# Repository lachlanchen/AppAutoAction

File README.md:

[English](README.md) · [العربية](i18n/README.ar.md) · [Español](i18n/README.es.md) · [Français](i18n/README.fr.md) · [日本語](i18n/README.ja.md) · [한국어](i18n/README.ko.md) · [Tiếng Việt](i18n/README.vi.md) · [中文 (简体)](i18n/README.zh-Hans.md) · [中文（繁體）](i18n/README.zh-Hant.md) · [Deutsch](i18n/README.de.md) · [Русский](i18n/README.ru.md)

<p align="center">

</p>

<h1 align="center">AgInTi LabCanvas</h1>

<p align="center">
  Agent routing for Blender, BioRender, Unity, Unreal, and future creative tools.
  AgInTi LabCanvas gives Codex, AgInTiFlow, Claude, local LLMs, and other MCP-aware agents one practical control plane for app automation.
</p>

<p align="center">
  <a href="#quick-start">Quick Start</a> ·
  <a href="#paper-figure-studio">Paper Figures</a> ·
  <a href="#3d-experiment-design">3D Design</a> ·
  <a href="#targets">Targets</a> ·
  <a href="#research-backed-design">Research</a> ·
  <a href="#languages">Languages</a>
</p>

<p align="center">
  Live studio demo: chat asks for a V-SPICE experiment setup, OpenSCAD exports the CAD proxy, and Blender renders the selected right-side canvas artifact.
</p>

## Why This Exists

Creative tools are gaining agent bridges, but each bridge has a different install path, port, protocol, and safety model. AgInTi LabCanvas keeps those targets in one registry, validates them, emits MCP client config, and dispatches dry-run or live JSON envelopes to the right adapter.

It is intentionally small: Python standard library, explicit config, no hidden editor automation.

## Quick Start

Install from npm:

```bash
npm install -g @lazyingart/labcanvas
labcanvas --version
labcanvas webapp start --port 19473
```

Or run from a source checkout:

```bash
PYTHONPATH=src python -m agenticapp list
PYTHONPATH=src python -m agenticapp doctor
PYTHONPATH=src python -m agenticapp dispatch blender "Create a red cube at the origin" --dry-run
PYTHONPATH=src python -m agenticapp mcp-config
PYTHONPATH=src python -m agenticapp studio status
PYTHONPATH=src python -m unittest discover -s tests
```

After installation, the console command is also available as:

```bash
labcanvas list
labcanvas dispatch unity "Create a test scene with three labeled cubes" --dry-run
labcanvas studio figure-grid "optical device icons 2x3" --rows 2 --cols 3
labcanvas webapp start --port 19473
```

## Paper Figure Studio

```bash
labcanvas web --port 8787 --open
```

The web app now has a bright-by-default theme, chat panel, artifact canvas, scene editor, and backend settings. It can:

- Switch the visible studio UI across the same 11 languages as the localized READMEs.
- Treat generated overview images as concepts, then decompose them into editable atomic parts.
- Generate exact `NxM` SVG paper-figure grids with black panel boundaries.
- Prepare AgInTi image-generation dry-run payloads for scientific icon concepts.
- Store BioRender MCP settings without storing secrets.
- Export the current scene to OpenSCAD for mechanical layout planning.
- Render the scene through Blender and preview PNG, `.blend`, `.scad`, JSON, and text artifacts.
- Toggle Blender, OpenSCAD, AgInTi image generation, BioRender MCP, and target-registry routing settings.
- Dry-run any configured target from the studio and save the dispatch envelope as a canvas artifact.

Artifacts are tracked under `output/webapp/artifacts.json` and served in the canvas rail. The intended figure architecture is documented in [docs/EDITABLE_FIGURE_PIPELINE.md](docs/EDITABLE_FIGURE_PIPELINE.md). See also [docs/PAPER_FIGURE_STUDIO.md](docs/PAPER_FIGURE_STUDIO.md), [docs/STUDIO_CLI.md](docs/STUDIO_CLI.md), [docs/WEBAPP.md](docs/WEBAPP.md), and [docs/NPM.md](docs/NPM.md).

## 3D Experiment Design

AgInTi LabCanvas now includes a systematic Blender workflow for paper setup figures, optical benches, device concepts, and experiment design:

```bash
labcanvas web --port 8787 --open
labcanvas scene-template experiment-setup --output my-setup.scene.json
labcanvas render-scene my-setup.scene.json --dry-run
labcanvas render-scene my-setup.scene.json --output-dir output/scenes
```

The web app provides chat, JSON scene editing, dry-run planning, and render preview. The source of truth is a JSON scene spec. Blender runs headless and produces a `.png` preview plus a `.blend` scene. Start from [examples/paper-optics-setup.scene.json](examples/paper-optics-setup.scene.json), inspect the generated [example render](examples/renders/paper-optics-setup.png), or read [docs/WEBAPP.md](docs/WEBAPP.md) and [docs/SCENE_SPEC.md](docs/SCENE_SPEC.md).

CAD hardware notes now live in [cad/README.md](cad/README.md), including the OpenHI/Nature STEP import notes and a parametric [C-mount reflector adapter](cad/designs/cmount_reflector_adapter/README.md). JLCPCB/Jialichuang automation research is documented in [pcb/jlcpcb-jialichuang-automation.md](pcb/jlcpcb-jialichuang-automation.md).

## Local Blender Test

For a no-sudo local Blender install and a real headless scene generation test:

```bash
scripts/install_blender_portable.sh
labcanvas --config configs/blender-local-command.example.json doctor
labcanvas --config configs/blender-local-command.example.json dispatch blender "Draw a welcoming modern building with a tower"
```

The command bridge is [bridges/codex_exec_blender.sh](bridges/codex_exec_blender.sh). It reads the AgInTi LabCanvas JSON envelope from stdin, runs Blender in background mode, stores Blender logs under `output/blender/`, and returns clean JSON with `.blend` and `.png` artifact paths.

## Targets

| Target | Current adapter | Best bridge shape | Notes |
| --- | --- | --- | --- |
| Blender | `http_json` | Blender MCP add-on, local HTTP, or command bridge | Good for scene generation, materials, rendering, export. |
| AgInTi | `local_command` via web settings | `aginti image --json` | Dry-run image payloads for figure concepts; live calls require provider keys. |
| BioRender | `browser` plus MCP metadata | Official remote MCP connector | Use OAuth/API-supported flows; avoid scraping. |
| Unity | `http_json` | Unity package, WebSocket proxy, or C# editor bridge | Good for scenes, assets, scripts, tests, play mode. |
| Unreal | `http_json` | Unreal MCP plugin or Python remote execution proxy | Treat as privileged editor access. |

Copy `configs/targets.example.json` to `labcanvas.targets.json` for local ports, commands, and tokens. This override file is ignored by git.

## Research-Backed Design

The design follows the MCP split between tools, resources, and prompts, then adapts it to live editor bridges. The research brief is in [docs/RESEARCH.md](docs/RESEARCH.md), covering:

- Blender MCP projects with headless and live-GUI modes.
- Unity MCP packages with scene, asset, script, and play-mode control.
- Unreal MCP servers using plugins or Python Remote Execution.
- BioRender's documented MCP connector endpoint.
- Security tradeoffs for agents with editor write access.

## Architecture

```text
Agent or MCP client
        |
        | command / dry-run / MCP config
        v
LabCanvas CLI
        |
        | target registry
        v
Transport adapter: http_json | local_command | browser | noop
        |
        v
Blender / BioRender / Unity / Unreal bridge
```

Every dispatch receives the same envelope:

```json
{
  "target": "blender",
  "kind": "blender",
  "instruction": "Create a red cube at the origin",
  "payload": {},
  "metadata": {
    "source": "labcanvas"
  }
}
```

## Languages

Localized READMEs live under `i18n/` and use the same profile-style language switcher as this root README:

[العربية](i18n/README.ar.md) · [Español](i18n/README.es.md) · [Français](i18n/README.fr.md) · [日本語](i18n/README.ja.md) · [한국어](i18n/README.ko.md) · [Tiếng Việt](i18n/README.vi.md) · [中文 (简体)](i18n/README.zh-Hans.md) · [中文（繁體）](i18n/README.zh-Hant.md) · [Deutsch](i18n/README.de.md) · [Русский](i18n/README.ru.md)

## Development

```bash
PYTHONPATH=src python -m unittest discover -s tests
PYTHONPATH=src python -m agenticapp doctor
```

Keep transport behavior covered by tests before adding live editor features. See [AGENTS.md](AGENTS.md) for contributor guidance and [SECURITY.md](SECURITY.md) for the editor-automation security model.

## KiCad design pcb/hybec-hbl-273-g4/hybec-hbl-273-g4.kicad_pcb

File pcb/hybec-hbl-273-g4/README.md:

# HYBEC HBL-273 / HBL-667 G4 Halogen Carrier PCB

This generated KiCad project adapts the existing NHI LED carrier style to a
two-hole direct-insertion G4 halogen lamp footprint.

- Board outline: circular, 24 mm diameter, matching the old LED carrier files.
- Mounting holes: four M2 NPTH holes at the same coordinates as the old boards.
- Lamp pins: two 1.20 mm plated holes on 4.00 mm G4 pitch.
- Power path: 1.20 mm top-layer copper tracks from the rear 1x02 input header.
- Lamp: 12 V, 20 W tungsten halogen, approximately 1.67 A.

Thermal note: a 20 W halogen lamp runs hot. Treat this PCB as a mechanical and
electrical adapter prototype; verify lamp standoff height, FR4 temperature,
airflow, and enclosure clearance before powering it in an instrument.

## Files

- `hybec-hbl-273-g4.kicad_pcb`: generated KiCad PCB.
- `hybec-hbl-273-hbl-667-lamp-dataset.json`: lamp specification dataset and source links.
- `artifacts/hybec-hbl-273-g4-render.png`: KiCad 3D render for review.
- `artifacts/hybec-hbl-273-g4-render-full.png`: zoomed-out full-board render.
- `artifacts/hybec-hbl-273-g4.step`: STEP export.
- `gerber/`: Gerber and Excellon drill outputs.

## Gerber Outputs

- `hybec-hbl-273-g4-F_Cu.gtl`, `hybec-hbl-273-g4-B_Cu.gbl`
- `hybec-hbl-273-g4-F_Mask.gts`, `hybec-hbl-273-g4-B_Mask.gbs`
- `hybec-hbl-273-g4-F_Silkscreen.gto`, `hybec-hbl-273-g4-B_Silkscreen.gbo`
- `hybec-hbl-273-g4-Edge_Cuts.gm1`
- `hybec-hbl-273-g4-job.gbrjob`
- `hybec-hbl-273-g4.drl`

## Reproduce

```bash
python3 pcb/scripts/generate_hybec_halogen_g4_board.py
kicad-cli pcb drc --format json --severity-all -o pcb/hybec-hbl-273-g4/artifacts/drc.json pcb/hybec-hbl-273-g4/hybec-hbl-273-g4.kicad_pcb
kicad-cli pcb export gerbers --layers F.Cu,B.Cu,F.SilkS,B.SilkS,F.Mask,B.Mask,Edge.Cuts,F.Fab,B.Fab --precision 6 -o pcb/hybec-hbl-273-g4/gerber pcb/hybec-hbl-273-g4/hybec-hbl-273-g4.kicad_pcb
kicad-cli pcb export drill --generate-map --map-format svg --generate-report --report-path pcb/hybec-hbl-273-g4/artifacts/drill-report.txt -o pcb/hybec-hbl-273-g4/gerber pcb/hybec-hbl-273-g4/hybec-hbl-273-g4.kicad_pcb
xvfb-run -a kicad-cli pcb render --output pcb/hybec-hbl-273-g4/artifacts/hybec-hbl-273-g4-render.png --width 1400 --height 1000 --background opaque --quality high --floor --perspective --rotate 315,0,35 --zoom 2.2 pcb/hybec-hbl-273-g4/hybec-hbl-273-g4.kicad_pcb
xvfb-run -a kicad-cli pcb render --output pcb/hybec-hbl-273-g4/artifacts/hybec-hbl-273-g4-render-full.png --width 1400 --height 1000 --background opaque --quality high --floor --perspective --rotate 315,0,35 --zoom 0.95 pcb/hybec-hbl-273-g4/hybec-hbl-273-g4.kicad_pcb
```

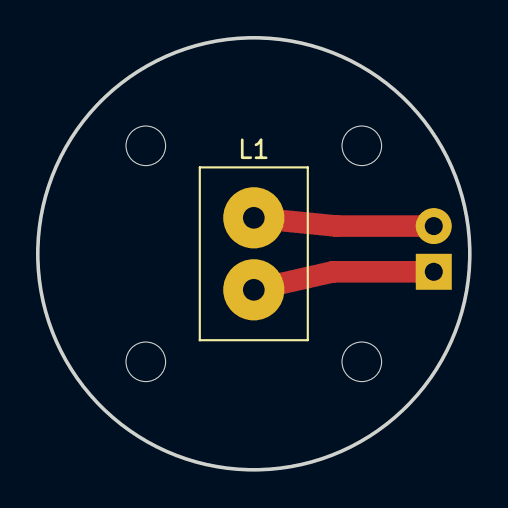
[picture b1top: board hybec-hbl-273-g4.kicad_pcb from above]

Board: 2 copper layers, 24.0 x 24.0 mm, 6 parts (1 on the bottom side), 2 nets.

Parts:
H1, H2, H3, H4: MountingHole; MountingHole_2.2mm_M2
J1: 12V_IN; PinHeader_1x02_P2.54mm_Horizontal
L1: HYBEC_HBL-273_G4_12V20W; HYBEC_HBL_273_G4_DirectPins

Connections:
HALOGEN_A_12V: J1.2 (A), L1.1 (A)
HALOGEN_B_RETURN: J1.1 (B), L1.2 (B)

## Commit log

2026-06-02 Add local Blender command bridge
2026-06-02 Add reusable Blender scene renderer
2026-06-02 Add paper figure artifact studio
2026-06-02 Document editable figure pipeline
2026-06-02 Add studio CLI parity
2026-06-02 Add V-SPICE studio demo screenshot
2026-06-02 Add localized README files
2026-06-02 Refresh README studio screenshot
2026-06-03 Add npm package wrapper
2026-06-03 Streamline npm releases
2026-06-04 Add GitHub funding links
2026-06-08 Document hybrid EM sensor roadmap
2026-06-09 Revise threaded reflector assembly geometry
2026-06-09 Version reflector assembly CAD artifacts
2026-06-10 Add editable CAD decomposition artifacts
2026-06-10 Split v2 CAD artifacts into run folders
2026-06-14 Rename project to AgInTi LabCanvas
2026-06-14 Document local npm token env setup
